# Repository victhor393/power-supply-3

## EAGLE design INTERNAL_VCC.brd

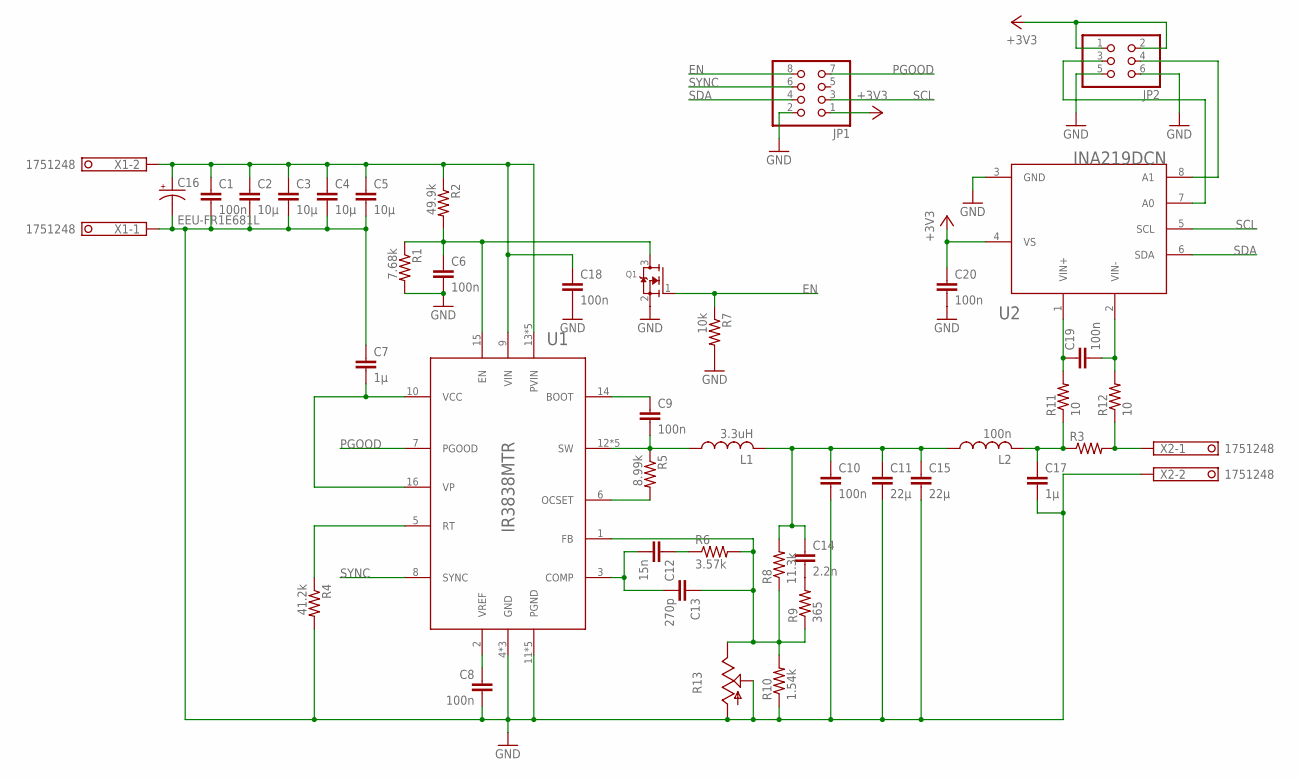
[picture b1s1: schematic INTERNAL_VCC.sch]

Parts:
C1, C6, C8, C9, C10, C18, C19, C20: 100n; C0603
C2, C3, C4, C5: 10µ; C1206
C7, C17: 1µ; C0603
C11, C15: 22µ; C1210
C12: 15n; C0603
C13: 270p; C0603
C14: 2.2n; C0603
C16: EEU-FR1E681L; E3,5-8
JP1: PINHD-2X4/90; 2X04/90
JP2: PINHD-2X3; 2X03
L1: 3.3uH; XAL7070
L2: 100n; SRP5030CA
Q1: MOSFET-NREFLOW; SOT23
R1: 7.68k; R0603
R2: 49.9k; R0603
R3: R-US_R2010; R2010
R4: 41.2k; R0603
R5: 8.99k; R0603
R6: 3.57k; R0603
R7: 10k; R0603
R8: 11.3k; R0603
R9: 365; R0603
R10: 1.54k; R0603
R11, R12: 10; R0603
R13: TRIM_US-B25P; B25P
U1: IR3838MTR; PQFN_5X6_MM
U2: INA219DCN; DCN-R-PDSO-G8
X1, X2: 1751248

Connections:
+3V3: C20.1, JP1.1, JP2.1, JP2.2, U2.4 (VS)
EN: JP1.8, Q1.1 (G), R7.1
GND: C1.2, C2.2, C3.2, C4.2, C5.2, C6.2, C7.1, C8.2, C10.2, C11.2, C15.2, C16.-, C17.2, C18.2, C20.2, JP1.2, JP2.5, JP2.6, Q1.2 (S), R1.2, R4.2, R7.2, R10.1, R13.A, R13.S, U1.4 (GND), U1.11 (PGND), U1.11@1 (PGND), U1.11@2 (PGND), U1.11@3 (PGND), U1.11@4 (PGND), U1.P$1 (GND), U1.P$26 (GND), U2.3 (GND), X1.1, X2.2
unnamed: C1.1, C2.1, C3.1, C4.1, C5.1, C16.+, C18.1, R2.1, U1.9 (VIN), U1.13 (PVIN), U1.13@1 (PVIN), U1.13@2 (PVIN), U1.13@3 (PVIN), U1.13@4 (PVIN), X1.2
unnamed: C17.1, L2.2, R3.1, R11.1
unnamed: C7.2, U1.10 (VCC), U1.16 (VP)
unnamed: R3.2, R12.1, X2.1
unnamed: C6.1, Q1.3 (D), R1.1, R2.2, U1.15 (EN)
unnamed: C8.1, U1.2 (VREF)
unnamed: R4.1, U1.5 (RT)
unnamed: C9.2, L1.1, L1.3 (1), R5.1, U1.12 (SW), U1.12@1 (SW), U1.12@2 (SW), U1.12@3 (SW), U1.12@4 (SW)
unnamed: C9.1, U1.14 (BOOT)
unnamed: R5.2, U1.6 (OCSET)
unnamed: C19.1, R11.2, U2.1 (VIN+)
unnamed: C12.2, C13.2, U1.3 (COMP)
unnamed: C12.1, R6.1
unnamed: C19.2, R12.2, U2.2 (VIN-)
unnamed: C13.1, R6.2, R8.1, R9.1, R10.2, R13.E, U1.1 (FB)
unnamed: C14.2, R9.2
unnamed: C10.1, C11.1, C14.1, C15.1, L1.2, L1.4 (2), L2.1, R8.2
unnamed: JP2.4, U2.8 (A1)
unnamed: JP2.3, U2.7 (A0)
PGOOD: JP1.7, U1.7 (PGOOD)
SCL: JP1.3, U2.5 (SCL)
SDA: JP1.4, U2.6 (SDA)
SYNC: JP1.6, U1.8 (SYNC)

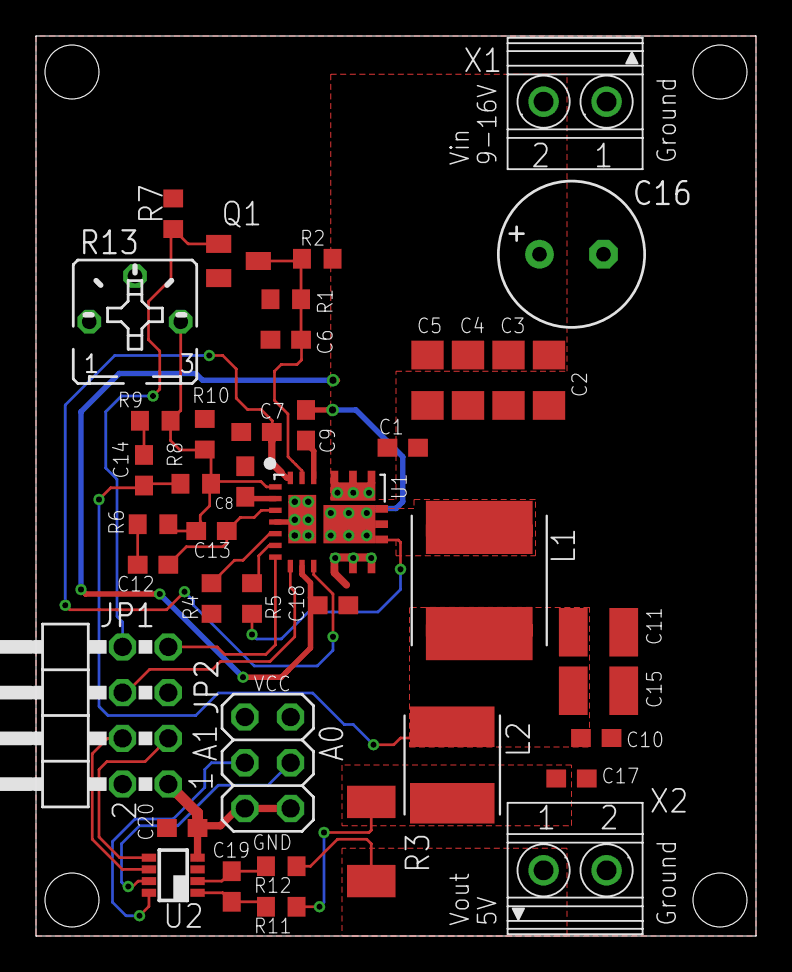
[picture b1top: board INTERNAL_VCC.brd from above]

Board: 2 copper layers, 40.0 x 50.0 mm, 42 parts (0 on the bottom side), 26 nets.

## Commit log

2019-05-21 Added schematic and board layout in pdf format
